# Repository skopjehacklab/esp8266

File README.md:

ESP8266 related stuff.

The main goal is to create a wifi-powered world domination army. First we are going to start by making all the lights in KIKA wifi powered. And then... profit.

https://www.youtube.com/watch?v=XpMb4OjVm_M

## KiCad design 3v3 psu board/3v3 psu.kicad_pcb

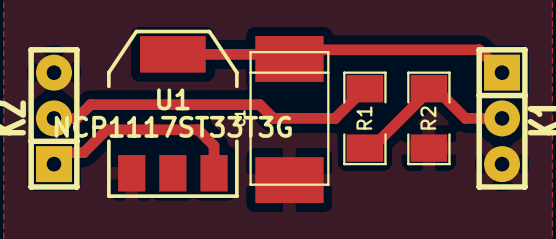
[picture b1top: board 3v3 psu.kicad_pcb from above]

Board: 2 copper layers, 6 parts (0 on the bottom side), 5 nets.

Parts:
C1: 10u; c_tant_D
K1: OUTPUT; SIL-3
K2: INPUT; SIL-3
R1: R; SM1206
R2: 1k; SM1206
U1: NCP1117ST33T3G; SOT223

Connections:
3V3: C1.1, K1.1, U1.2, U1.4
5V: K2.1, U1.3
GND: C1.2, K1.3, K2.3, R2.2, U1.1
RX_wifi: K1.2, R1.2, R2.1
TX_uC: K2.2, R1.1

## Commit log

2014-12-20 dump
2014-12-20 rename
2014-12-20 Random reade
